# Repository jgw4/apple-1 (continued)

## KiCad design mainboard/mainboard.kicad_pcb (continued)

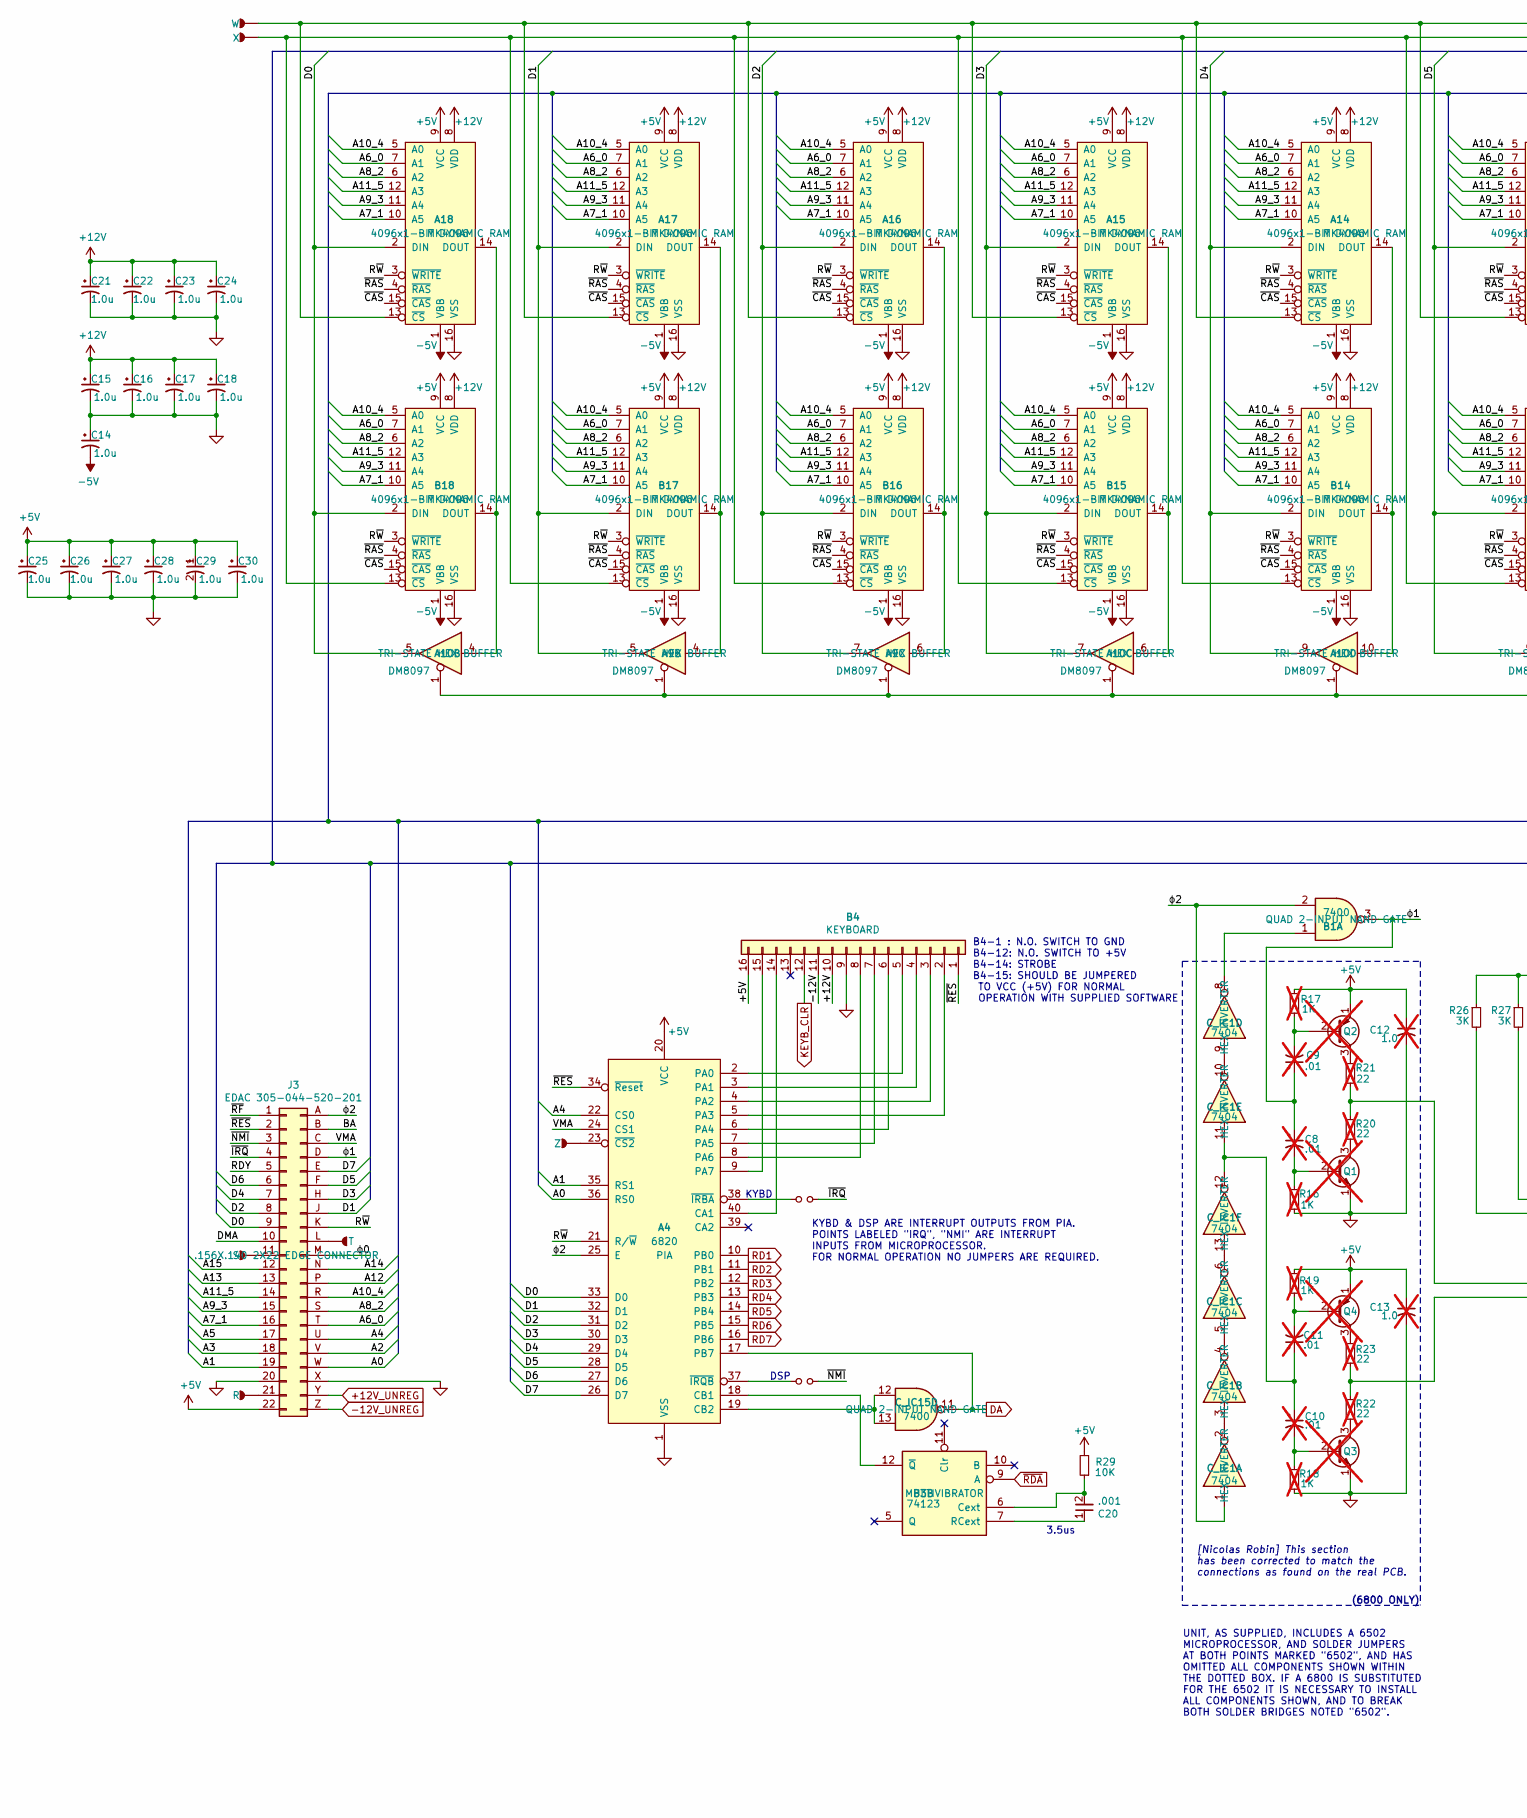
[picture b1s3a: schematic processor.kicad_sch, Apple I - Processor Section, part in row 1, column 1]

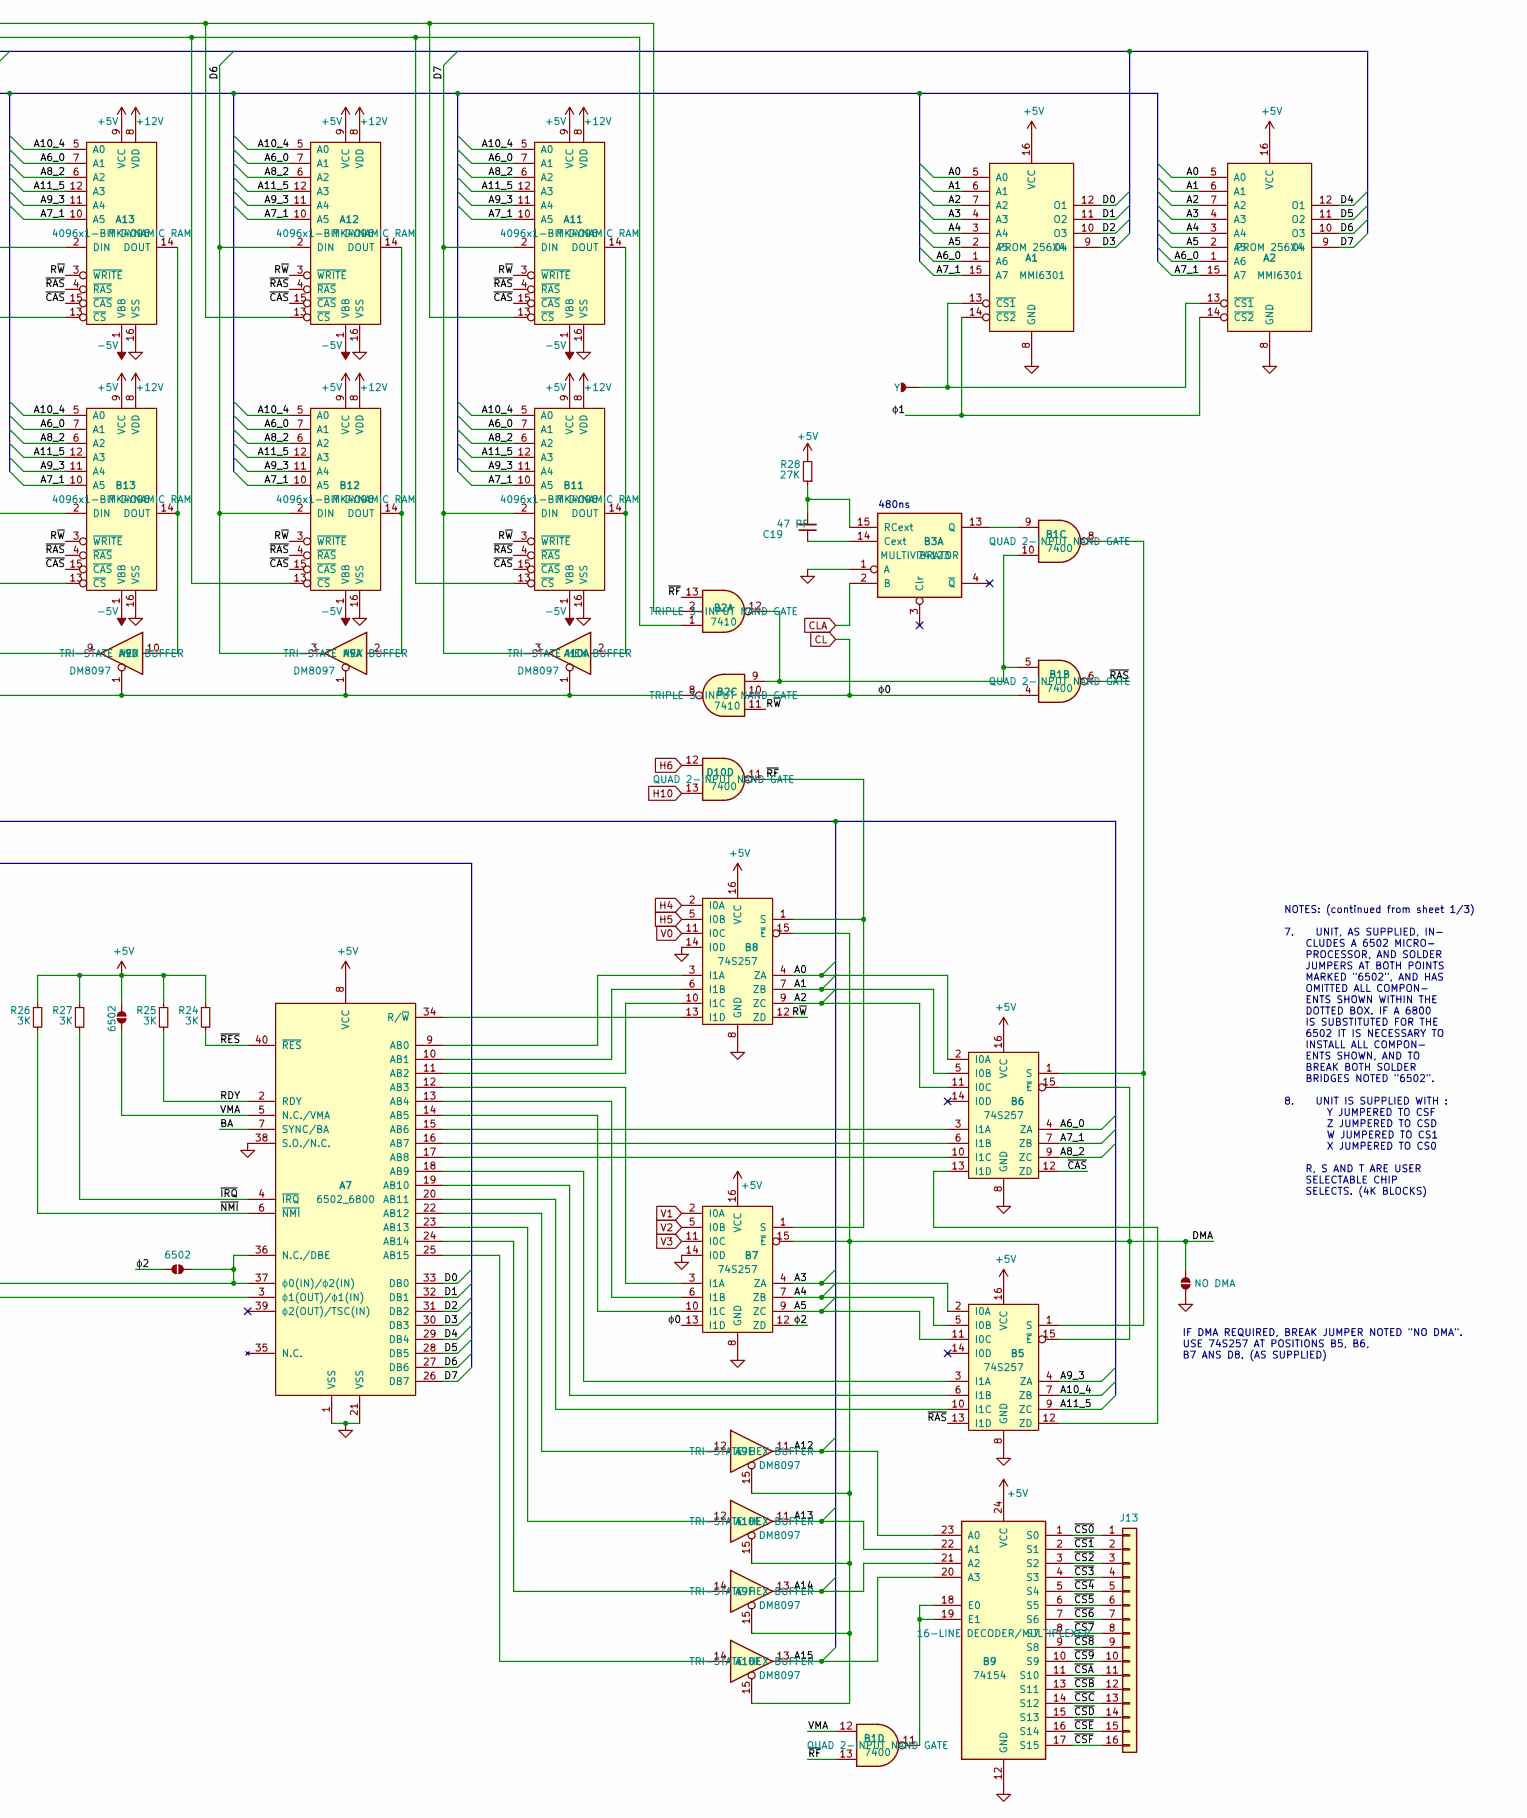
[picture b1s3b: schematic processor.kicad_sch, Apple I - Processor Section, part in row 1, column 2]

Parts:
A1, A2: MMI6301; apple-1_DIP-16_W7.62mm
A4: 6820; apple-1_DIP-40_W15.24mm
A7: 6502_6800; apple-1_DIP-40_W15.24mm
A9, A10: DM8097; apple-1_DIP-16_W7.62mm
A11, A12, A13, A14, A15, A16, A17, A18: MK4096; apple-1_DIP-16_W7.62mm
B1: 7400; apple-1_DIP-14_W7.62mm
B2: 7410; apple-1_DIP-14_W7.62mm
B3: 74123; apple-1_DIP-16_W7.62mm
B4: KEYBOARD; apple-1_DIP-16_W7.62mm
B5, B6, B7, B8: 74S257; apple-1_DIP-16_W7.62mm
B9: 74154; apple-1_DIP-24_18.0mmx34.29mm_W15.24mm
B11, B12, B13, B14, B15, B16, B17, B18: MK4096; apple-1_DIP-16_W7.62mm
C8, C9, C10, C11: .01; apple-1_C_Disc_D16.0mm_W5.0mm_P7.50mm (68000 section); not fitted
C12, C13: 1.0; apple-1_C_Disc_D16.0mm_W5.0mm_P7.50mm (68000 section); not fitted
C14, C25, C26, C27, C28, C29, C30: 1.0u; apple-1_C_Disc_D16.0mm_W5.0mm_P7.50mm
C15, C16, C17, C18, C21, C22, C23, C24: 1.0u; apple-1_C_Disc_D16.0mm_W5.0mm_P275mils
C19: 47 PF; apple-1_C_Disc_D16.0mm_W5.0mm_P7.50mm
C20: .001; apple-1_C_Disc_D16.0mm_W5.0mm_P7.50mm
C_IC1: 7404; apple-1_DIP-14_W7.62mm
C_IC15: 7400; apple-1_DIP-14_W7.62mm
D10: 7400; apple-1_DIP-14_W7.62mm
J3: EDAC 305-044-520-201; 307044520201
J4: W; WJumper
J5: X; XJumper
J6: S; SJumper
J7: R; RJumper
J8: T; TJumper
J9: Z; ZJumper
J10, J11: 6502
J12: Y; YJumper
J13: Conn_01x16; J13
J14: NO DMA
JP1: Jumper_NO_Small; apple-1_KBD-IRQ
JP2: Jumper_NO_Small; apple-1_DSP-NMI
Q1, Q3: Q_NPN_EBC; apple-1_TO-92_HandSolder; not fitted
Q2, Q4: Q_PNP_EBC; apple-1_TO-92_HandSolder; not fitted
R16, R17, R18, R19: 1K; apple-1_R_Axial_DIN0207_L6.3mm_D2.5mm_P10.16mm_Horizontal; not fitted
R20, R21, R22, R23: 22; apple-1_R_Axial_DIN0207_L6.3mm_D2.5mm_P10.16mm_Horizontal; not fitted
R24, R25, R26, R27: 3K; apple-1_R_Axial_DIN0207_L6.3mm_D2.5mm_P10.16mm_Horizontal
R28: 27K; apple-1_R_Axial_DIN0207_L6.3mm_D2.5mm_P10.16mm_Horizontal
R29: 10K; apple-1_R_Axial_DIN0207_L6.3mm_D2.5mm_P10.16mm_Horizontal

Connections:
+5V: A1.16 (VCC), A2.16 (VCC), A4.20 (VCC), A7.8 (VCC), A11.9 (VCC), A12.9 (VCC), A13.9 (VCC), A14.9 (VCC), A15.9 (VCC), A16.9 (VCC), A17.9 (VCC), A18.9 (VCC), B4.16, B5.16 (VCC), B6.16 (VCC), B7.16 (VCC), B8.16 (VCC), B9.24 (VCC), B11.9 (VCC), B12.9 (VCC), B13.9 (VCC), B14.9 (VCC), B15.9 (VCC), B16.9 (VCC), B17.9 (VCC), B18.9 (VCC), C12.1, C13.1, C25.1, C26.1, C27.1, C28.1, C29.1, C30.1, J3.22, J10.1, Q2.1 (E), Q4.1 (E), R17.2, R19.2, R24.1, R25.1, R26.1, R27.1, R28.2, R29.2; also elsewhere on the board
+12V: A11.8 (VDD), A12.8 (VDD), A13.8 (VDD), A14.8 (VDD), A15.8 (VDD), A16.8 (VDD), A17.8 (VDD), A18.8 (VDD), B4.10, B11.8 (VDD), B12.8 (VDD), B13.8 (VDD), B14.8 (VDD), B15.8 (VDD), B16.8 (VDD), B17.8 (VDD), B18.8 (VDD), C15.1, C16.1, C17.1, C18.1, C21.1, C22.1, C23.1, C24.1; also elsewhere on the board
+12V_UNREG: J3.Y; also elsewhere on the board
-5V: A11.1 (VBB), A12.1 (VBB), A13.1 (VBB), A14.1 (VBB), A15.1 (VBB), A16.1 (VBB), A17.1 (VBB), A18.1 (VBB), B11.1 (VBB), B12.1 (VBB), B13.1 (VBB), B14.1 (VBB), B15.1 (VBB), B16.1 (VBB), B17.1 (VBB), B18.1 (VBB), C14.2; also elsewhere on the board
-12V_UNREG: J3.Z; also elsewhere on the board
/Processor Section/-12V: B4.11
/Processor Section/A0: A1.5 (A0), A2.5 (A0), A4.36 (RS0), B6.2 (I0A), B8.4 (ZA), J3.W
/Processor Section/A1: A1.6 (A1), A2.6 (A1), A4.35 (RS1), B6.5 (I0B), B8.7 (ZB), J3.19
/Processor Section/A2: A1.7 (A2), A2.7 (A2), B6.11 (I0C), B8.9 (ZC), J3.V
/Processor Section/A3: A1.4 (A3), A2.4 (A3), B5.2 (I0A), B7.4 (ZA), J3.18
/Processor Section/A4: A1.3 (A4), A2.3 (A4), A4.22 (CS0), B5.5 (I0B), B7.7 (ZB), J3.U
/Processor Section/A5: A1.2 (A5), A2.2 (A5), B5.11 (I0C), B7.9 (ZC), J3.17
/Processor Section/A6_0: A1.1 (A6), A2.1 (A6), A11.7 (A1), A12.7 (A1), A13.7 (A1), A14.7 (A1), A15.7 (A1), A16.7 (A1), A17.7 (A1), A18.7 (A1), B6.4 (ZA), B11.7 (A1), B12.7 (A1), B13.7 (A1), B14.7 (A1), B15.7 (A1), B16.7 (A1), B17.7 (A1), B18.7 (A1), J3.T
/Processor Section/A7_1: A1.15 (A7), A2.15 (A7), A11.10 (A5), A12.10 (A5), A13.10 (A5), A14.10 (A5), A15.10 (A5), A16.10 (A5), A17.10 (A5), A18.10 (A5), B6.7 (ZB), B11.10 (A5), B12.10 (A5), B13.10 (A5), B14.10 (A5), B15.10 (A5), B16.10 (A5), B17.10 (A5), B18.10 (A5), J3.16
/Processor Section/A8_2: A11.6 (A2), A12.6 (A2), A13.6 (A2), A14.6 (A2), A15.6 (A2), A16.6 (A2), A17.6 (A2), A18.6 (A2), B6.9 (ZC), B11.6 (A2), B12.6 (A2), B13.6 (A2), B14.6 (A2), B15.6 (A2), B16.6 (A2), B17.6 (A2), B18.6 (A2), J3.S
/Processor Section/A9_3: A11.11 (A4), A12.11 (A4), A13.11 (A4), A14.11 (A4), A15.11 (A4), A16.11 (A4), A17.11 (A4), A18.11 (A4), B5.4 (ZA), B11.11 (A4), B12.11 (A4), B13.11 (A4), B14.11 (A4), B15.11 (A4), B16.11 (A4), B17.11 (A4), B18.11 (A4), J3.15
/Processor Section/A10_4: A11.5 (A0), A12.5 (A0), A13.5 (A0), A14.5 (A0), A15.5 (A0), A16.5 (A0), A17.5 (A0), A18.5 (A0), B5.7 (ZB), B11.5 (A0), B12.5 (A0), B13.5 (A0), B14.5 (A0), B15.5 (A0), B16.5 (A0), B17.5 (A0), B18.5 (A0), J3.R
/Processor Section/A11_5: A11.12 (A3), A12.12 (A3), A13.12 (A3), A14.12 (A3), A15.12 (A3), A16.12 (A3), A17.12 (A3), A18.12 (A3), B5.9 (ZC), B11.12 (A3), B12.12 (A3), B13.12 (A3), B14.12 (A3), B15.12 (A3), B16.12 (A3), B17.12 (A3), B18.12 (A3), J3.14
/Processor Section/A12: A9.11, B9.23 (A0), J3.P
/Processor Section/A13: A10.11, B9.22 (A1), J3.13
/Processor Section/A14: A9.13, B9.21 (A2), J3.N
/Processor Section/A15: A10.13, B9.20 (A3), J3.12
/Processor Section/BA: A7.7 (SYNC/BA), J3.B
/Processor Section/D0: A1.12 (O1), A4.33 (D0), A7.33 (DB0), A10.5, A18.2 (DIN), B18.2 (DIN), J3.9
/Processor Section/D1: A1.11 (O2), A4.32 (D1), A7.32 (DB1), A9.5, A17.2 (DIN), B17.2 (DIN), J3.J
/Processor Section/D2: A1.10 (O3), A4.31 (D2), A7.31 (DB2), A9.7, A16.2 (DIN), B16.2 (DIN), J3.8
/Processor Section/D3: A1.9 (O4), A4.30 (D3), A7.30 (DB3), A10.7, A15.2 (DIN), B15.2 (DIN), J3.H
/Processor Section/D4: A2.12 (O1), A4.29 (D4), A7.29 (DB4), A10.9, A14.2 (DIN), B14.2 (DIN), J3.7
/Processor Section/D5: A2.11 (O2), A4.28 (D5), A7.28 (DB5), A9.9, A13.2 (DIN), B13.2 (DIN), J3.F
/Processor Section/D6: A2.10 (O3), A4.27 (D6), A7.27 (DB6), A9.3, A12.2 (DIN), B12.2 (DIN), J3.6
/Processor Section/D7: A2.9 (O4), A4.26 (D7), A7.26 (DB7), A10.3, A11.2 (DIN), B11.2 (DIN), J3.E
/Processor Section/DMA: A9.15, A10.15, B5.15 (~E), B6.15 (~E), B7.15 (~E), B8.15 (~E), J3.10, J14.1
/Processor Section/RDY: A7.2 (RDY), J3.5, R25.2
/Processor Section/R~W: A4.21 (R/~W), A11.3 (~WRITE), A12.3 (~WRITE), A13.3 (~WRITE), A14.3 (~WRITE), A15.3 (~WRITE), A16.3 (~WRITE), A17.3 (~WRITE), A18.3 (~WRITE), B2.11, B8.12 (ZD), B11.3 (~WRITE), B12.3 (~WRITE), B13.3 (~WRITE), B14.3 (~WRITE), B15.3 (~WRITE), B16.3 (~WRITE), B17.3 (~WRITE), B18.3 (~WRITE), J3.K
/Processor Section/VMA: A4.24 (CS1), A7.5 (N.C./VMA), B1.12, J3.C, J10.2
/Processor Section/~CAS: A11.15 (~CAS), A12.15 (~CAS), A13.15 (~CAS), A14.15 (~CAS), A15.15 (~CAS), A16.15 (~CAS), A17.15 (~CAS), A18.15 (~CAS), B6.12 (ZD), B11.15 (~CAS), B12.15 (~CAS), B13.15 (~CAS), B14.15 (~CAS), B15.15 (~CAS), B16.15 (~CAS), B17.15 (~CAS), B18.15 (~CAS)
/Processor Section/~CS0: B9.1 (S0), J13.1
/Processor Section/~CS1: B9.2 (S1), J13.2
/Processor Section/~CS2: B9.3 (S2), J13.3
/Processor Section/~CS3: B9.4 (S3), J13.4
/Processor Section/~CS4: B9.5 (S4), J13.5
/Processor Section/~CS5: B9.6 (S5), J13.6
/Processor Section/~CS6: B9.7 (S6), J13.7
/Processor Section/~CS7: B9.8 (S7), J13.8
/Processor Section/~CS8: B9.9 (S8), J13.9
/Processor Section/~CS9: B9.10 (S9), J13.10
/Processor Section/~CSA: B9.11 (S10), J13.11
/Processor Section/~CSB: B9.13 (S11), J13.12
/Processor Section/~CSC: B9.14 (S12), J13.13
/Processor Section/~CSD: B9.15 (S13), J13.14
/Processor Section/~CSE: B9.16 (S14), J13.15
/Processor Section/~CSF: B9.17 (S15), J13.16
/Processor Section/~IRQ: A7.4 (~IRQ), J3.4, JP1.2, R27.2
/Processor Section/~NMI: A7.6 (~NMI), J3.3, JP2.2, R26.2
/Processor Section/~RAS: A11.4 (~RAS), A12.4 (~RAS), A13.4 (~RAS), A14.4 (~RAS), A15.4 (~RAS), A16.4 (~RAS), A17.4 (~RAS), A18.4 (~RAS), B1.6, B5.13 (I1D), B11.4 (~RAS), B12.4 (~RAS), B13.4 (~RAS), B14.4 (~RAS), B15.4 (~RAS), B16.4 (~RAS), B17.4 (~RAS), B18.4 (~RAS)
/Processor Section/~RES: A4.34 (~Reset), A7.40 (~RES), B4.1, J3.2, R24.2
/Processor Section/~RF: B1.13, B2.13, B7.1 (S), B8.1 (S), D10.11, J3.1
/Processor Section/ɸ1: A1.14 (~CS2), A2.14 (~CS2), B1.3, C8.1, C9.1, J3.D
/Processor Section/ɸ2: A4.25 (E), B1.2, B7.12 (ZD), C_IC1.1, J3.A, J11.2
CL: B1.4, B2.10, B7.13 (I1D), J3.M; also elsewhere on the board
CLA: B3.2 (B); also elsewhere on the board
DA: A4.17 (PB7), C_IC15.11; also elsewhere on the board
H4: B8.2 (I0A); also elsewhere on the board
H5: B8.5 (I0B); also elsewhere on the board
H6: D10.12; also elsewhere on the board
H10: D10.13; also elsewhere on the board
KEYB_CLR: B4.12; also elsewhere on the board
unnamed: A1.13 (~CS1), A2.13 (~CS1), J12.1
unnamed: A4.40 (CA1), B4.14
unnamed: A4.18 (CB1), B3.12 (~Q)
unnamed: A4.19 (CB2), C_IC15.12, C_IC15.13
unnamed: A4.2 (PA0), B4.5
unnamed: A4.3 (PA1), B4.4
unnamed: A4.4 (PA2), B4.3
unnamed: A4.5 (PA3), B4.2
unnamed: A4.6 (PA4), B4.6
unnamed: A4.7 (PA5), B4.7
unnamed: A4.8 (PA6), B4.8
unnamed: A4.9 (PA7), B4.15
unnamed: A4.23 (~CS2), J9.1
unnamed: A4.38 (~IRBA), JP1.1
unnamed: A4.37 (~IRQB), JP2.1
unnamed: A7.9 (AB0), B8.3 (I1A)
unnamed: A7.10 (AB1), B8.6 (I1B)
unnamed: A7.11 (AB2), B8.10 (I1C)
unnamed: A7.12 (AB3), B7.3 (I1A)
unnamed: A7.13 (AB4), B7.6 (I1B)
unnamed: A7.14 (AB5), B7.10 (I1C)
unnamed: A7.15 (AB6), B6.3 (I1A)
unnamed: A7.16 (AB7), B6.6 (I1B)
unnamed: A7.17 (AB8), B6.10 (I1C)
unnamed: A7.18 (AB9), B5.3 (I1A)
unnamed: A7.19 (AB10), B5.6 (I1B)
unnamed: A7.20 (AB11), B5.10 (I1C)
unnamed: A7.22 (AB12), A9.12
unnamed: A7.23 (AB13), A10.12
unnamed: A7.24 (AB14), A9.14
unnamed: A7.25 (AB15), A10.14
unnamed: A7.36 (N.C./DBE), A7.37 (ɸ0(IN)/ɸ2(IN)), J11.1, R20.1, R21.2
unnamed: A7.34 (R/~W), B8.13 (I1D)
unnamed: A7.3 (ɸ1(OUT)/ɸ1(IN)), R22.1, R23.2
unnamed: A9.1, A10.1, B2.8
unnamed: A10.2, A11.14 (DOUT), B11.14 (DOUT)
unnamed: A11.13 (~CS), A12.13 (~CS), A13.13 (~CS), A14.13 (~CS), A15.13 (~CS), A16.13 (~CS), A17.13 (~CS), A18.13 (~CS), B2.2, J4.1
unnamed: A9.2, A12.14 (DOUT), B12.14 (DOUT)
unnamed: A9.10, A13.14 (DOUT), B13.14 (DOUT)
unnamed: A10.10, A14.14 (DOUT), B14.14 (DOUT)
unnamed: A10.6, A15.14 (DOUT), B15.14 (DOUT)
unnamed: A9.6, A16.14 (DOUT), B16.14 (DOUT)
unnamed: A9.4, A17.14 (DOUT), B17.14 (DOUT)
unnamed: A10.4, A18.14 (DOUT), B18.14 (DOUT)
unnamed: B1.1, C_IC1.8
unnamed: B1.5, B1.10, B2.9, B2.12
unnamed: B3.14 (Cext), C19.1
unnamed: B1.9, B3.13 (Q)
unnamed: B3.15 (RCext), C19.2, R28.1
unnamed: B3.6 (Cext), C20.2, R29.1
unnamed: B3.7 (RCext), C20.1
unnamed: B1.8, B5.1 (S), B6.1 (S)
unnamed: B5.12 (ZD), B6.13 (I1D)
unnamed: B1.11, B9.18 (E0), B9.19 (E1)
unnamed: B2.1, B11.13 (~CS), B12.13 (~CS), B13.13 (~CS), B14.13 (~CS), B15.13 (~CS), B16.13 (~CS), B17.13 (~CS), B18.13 (~CS), J5.1
unnamed: C10.1, C11.1, C_IC1.11, C_IC1.12
unnamed: C_IC1.2, C_IC1.3
unnamed: C_IC1.4, C_IC1.5
unnamed: C_IC1.9, C_IC1.10
unnamed: C_IC1.6, C_IC1.13
unnamed: J3.11, J6.1
unnamed: J3.21, J7.1 (~_1)
unnamed: J3.L, J8.1
unnamed: C8.2, Q1.2 (B), R16.1
unnamed: Q1.3 (C), R20.2
unnamed: C9.2, Q2.2 (B), R17.1
unnamed: Q2.3 (C), R21.1
unnamed: C10.2, Q3.2 (B), R18.1
unnamed: Q3.3 (C), R22.2
unnamed: C11.2, Q4.2 (B), R19.1
unnamed: Q4.3 (C), R23.1
RD1: A4.10 (PB0); also elsewhere on the board
RD2: A4.11 (PB1); also elsewhere on the board
RD3: A4.12 (PB2); also elsewhere on the board
RD4: A4.13 (PB3); also elsewhere on the board
RD5: A4.14 (PB4); also elsewhere on the board
RD6: A4.15 (PB5); also elsewhere on the board
RD7: A4.16 (PB6); also elsewhere on the board
V0: B8.11 (I0C); also elsewhere on the board
V1: B7.2 (I0A); also elsewhere on the board
V2: B7.5 (I0B); also elsewhere on the board
V3: B7.11 (I0C); also elsewhere on the board
~RDA: B3.9 (A); also elsewhere on the board

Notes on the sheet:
[Nicolas Robin] This section has been corrected to match the connections as found on the real PCB.
UNIT, AS SUPPLIED, INCLUDES A 6502 MICROPROCESSOR, AND SOLDER JUMPERS AT BOTH POINTS MARKED "6502", AND HAS OMITTED ALL COMPONENTS SHOWN WITHIN THE DOTTED BOX. IF A 6800 IS SUBSTITUTED FOR THE 6502 IT IS NECESSARY TO INSTALL ALL COMPONENTS SHOWN, AND TO BREAK BOTH SOLDER BRIDGES NOTED "6502".
DSP
KYBD
KYBD & DSP ARE INTERRUPT OUTPUTS FROM PIA. POINTS LABELED "IRQ", "NMI" ARE INTERRUPT INPUTS FROM MICROPROCESSOR. FOR NORMAL OPERATION NO JUMPERS ARE REQUIRED.
NOTES: (continued from sheet 1/3) 7. UNIT, AS SUPPLIED, IN- CLUDES A 6502 MICRO- PROCESSOR, AND SOLDER JUMPERS AT BOTH POINTS MARKED "6502", AND HAS OMITTED ALL COMPON- ENTS SHOWN WITHIN THE DOTTED BOX. IF A 6800 IS SUBSTITUTED FOR THE 6502 IT IS NECESSARY TO INSTALL ALL COMPON- ENTS SHOWN, AND TO 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
(6800 ONLY)
IF DMA REQUIRED, BREAK JUMPER NOTED "NO DMA". USE 74S257 AT POSITIONS B5, B6, B7 ANS D8. (AS SUPPLIED)
B4-1 : N.O. SWITCH TO GND B4-12: N.O. SWITCH TO +5V B4-14: STROBE B4-15: SHOULD BE JUMPERED TO VCC (+5V) FOR NORMAL OPERATION WITH SUPPLIED SOFTWARE
480ns
3.5us

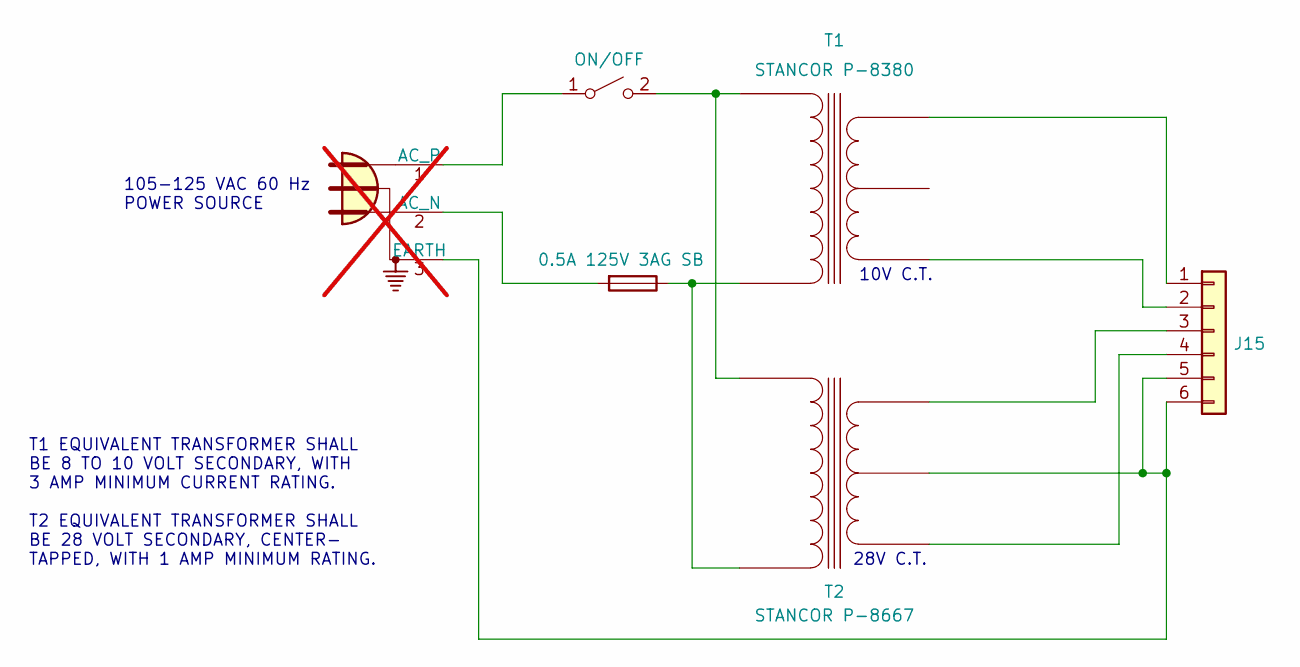
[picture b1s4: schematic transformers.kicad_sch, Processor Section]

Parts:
F1: 0.5A 125V 3AG SB
J15: Conn_01x06
P1: Conn_WallPlug_Earth; not fitted
SW1: ON/OFF
T1: STANCOR P-8380
T2: STANCOR P-8667

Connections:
unnamed 217: T1.~; also elsewhere on the board
unnamed 219: T1.~; also elsewhere on the board
unnamed 220: T2.~; also elsewhere on the board
unnamed 221: T2.~; also elsewhere on the board
unnamed: F1.1, T1.~, T2.~
unnamed: F1.2, P1.2 (AC_N)
unnamed: P1.1 (AC_P), SW1.1 (A)
unnamed: SW1.2 (B), T1.~, T2.~

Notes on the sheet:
10V C.T.
28V C.T.
105-125 VAC 60 Hz POWER SOURCE
T1 EQUIVALENT TRANSFORMER SHALL BE 8 TO 10 VOLT SECONDARY, WITH 3 AMP MINIMUM CURRENT RATING. T2 EQUIVALENT TRANSFORMER SHALL BE 28 VOLT SECONDARY, CENTER- TAPPED, WITH 1 AMP MINIMUM RATING.

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
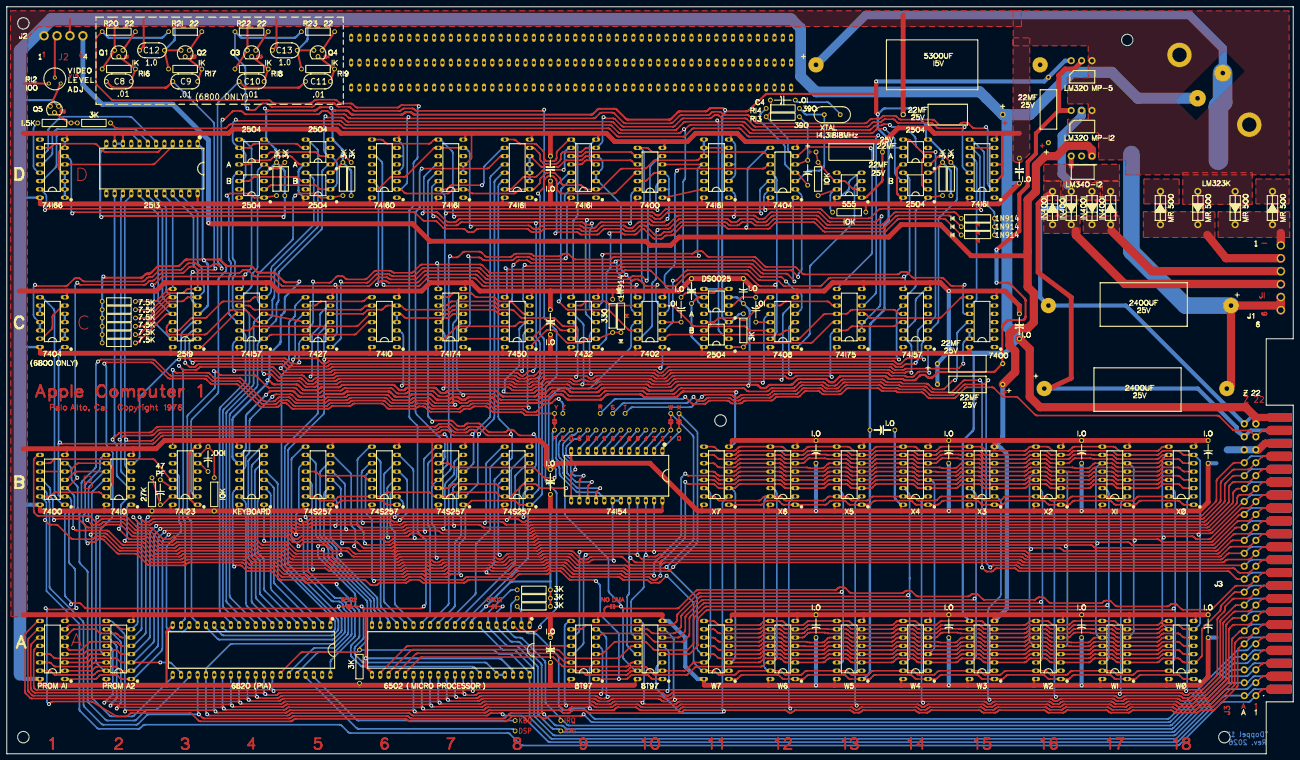
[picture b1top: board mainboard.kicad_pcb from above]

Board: 2 copper layers, 393.7 x 228.6 mm, 170 parts (0 on the bottom side), 245 nets.
